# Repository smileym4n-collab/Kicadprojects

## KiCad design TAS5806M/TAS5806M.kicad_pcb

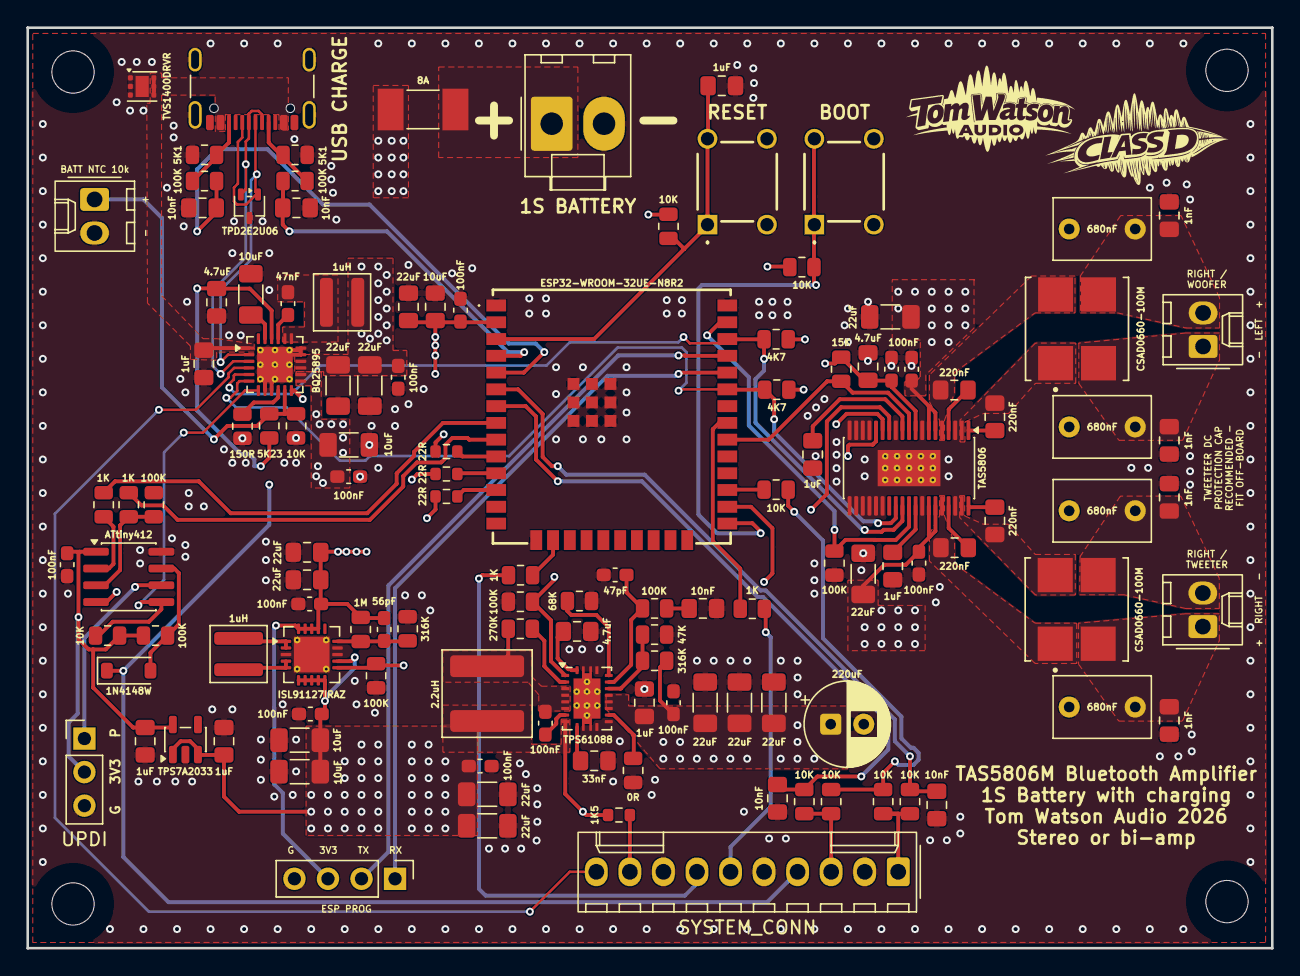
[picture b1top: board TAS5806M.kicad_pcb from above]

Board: 4 copper layers, 94.2 x 69.7 mm, 130 parts (0 on the bottom side), 82 nets.

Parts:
C101, C102, C204, C404, C405: 10nF; C_0805_2012Metric_Pad1.18x1.45mm_HandSolder
C103, C109, C302, C303: 10uF; C_1206_3216Metric_Pad1.33x1.80mm_HandSolder
C104: 47nF; C_0603_1608Metric_Pad1.08x0.95mm_HandSolder
C105, C209, C401, C402, C501, C614, C615: 1uF; C_0805_2012Metric_Pad1.18x1.45mm_HandSolder
C106, C107, C206, C207, C210, C211, C212, C616, C618: 22uF; C_1206_3216Metric_Pad1.33x1.80mm_HandSolder
C108, C111, C201, C208, C213, C304, C307, C403, C504, C617, C619, C622: 100nF; C_0603_1608Metric_Pad1.08x0.95mm_HandSolder
C110, C202, C621: 4.7uF; C_0805_2012Metric_Pad1.18x1.45mm_HandSolder
C203: 33nF; C_0805_2012Metric_Pad1.18x1.45mm_HandSolder
C205: 47pF; C_0603_1608Metric_Pad1.08x0.95mm_HandSolder
C301: 56pF; C_0603_1608Metric_Pad1.08x0.95mm_HandSolder
C305, C306, C502: 22uF; C_0805_2012Metric_Pad1.18x1.45mm_HandSolder
C503: 10uF; C_0805_2012Metric_Pad1.18x1.45mm_HandSolder
C601, C602, C607, C608: 220nF; C_0805_2012Metric_Pad1.18x1.45mm_HandSolder
C603, C604, C609, C610: 680nF; C_Rect_L7.2mm_W4.5mm_P5.00mm_FKS2_FKP2_MKS2_MKP2
C605, C606, C611, C612: 1nF; C_0805_2012Metric_Pad1.18x1.45mm_HandSolder
C620: 220uF; CP_Radial_D6.3mm_P2.50mm
D101: TVS1400DRVR; WSON-6-1EP_2x2mm_P0.65mm_EP1x1.6mm
D401: 1N4148W; D_SOD-123
F101: 8A; Fuse_Littelfuse-NANO2-451_453
H1, H2, H3, H4: MountingHole; MountingHole_3.2mm_M3
J1: ESP PROG; PinHeader_1x04_P2.54mm_Vertical
J2: UPDI; PinHeader_1x03_P2.54mm_Vertical
J101: USB CHARGE; USB_C_Receptacle_GCT_USB4105-xx-A_16P_TopMnt_Horizontal
J102: 1S BATTERY; Molex_KK-396_A-41791-0002_1x02_P3.96mm_Vertical
J103: BATT NTC 10k; Molex_KK-254_AE-6410-02A_1x02_P2.54mm_Vertical
J402: SYSTEM_CONN; Molex_KK-254_AE-6410-10A_1x10_P2.54mm_Vertical
J601: - LEFT +; Molex_KK-254_AE-6410-02A_1x02_P2.54mm_Vertical
J602: + RIGHT -; Molex_KK-254_AE-6410-02A_1x02_P2.54mm_Vertical
L101, L301: 1uH; L_Wuerth_MAPI-4020
L201: 2.2uH; L_Bourns_SRP6060FA_BournsLayout
L601, L602: CSAD0660-100M
R101: 150R; R_0805_2012Metric
R102, R104: 5K1; R_0805_2012Metric
R103, R105, R204, R207, R302, R402, R405, R602: 100K; R_0805_2012Metric
R106: 1K5; R_0603_1608Metric
R107: 5K23; R_0805_2012Metric
R108, R401, R406, R407, R408, R409, R501, R506, R510: 10K; R_0805_2012Metric
R201, R304: 316K; R_0805_2012Metric
R202: 47K; R_0805_2012Metric
R203: 270K; R_0805_2012Metric
R205: 0R; R_0805_2012Metric
R206: 68K; R_0805_2012Metric
R303: 1M; R_0805_2012Metric
R403, R404, R505, R509: 1K; R_0805_2012Metric
R502, R503, R504: 22R; R_0603_1608Metric
R507, R508: 4K7; R_0805_2012Metric
R601: 15K; R_0805_2012Metric
SW501: RESET; TS026650BK100SCRD
SW502: BOOT; TS026650BK100SCRD
U101: BQ25895; Texas_RTW_WQFN-24-1EP_4x4mm_P0.5mm_EP2.7x2.7mm_ThermalVias
U102: TPD2E2U06; SOT-323_SC-70
U201: TPS61088; Texas_VQFN-RHL-20_ThermalVias
U301: ISL91127IRAZ; QFN-20-1EP_4x4mm_P0.5mm_EP2.7x2.7mm_ThermalVias
U401: TPS7A2033; SOT-23-5
U402: ATtiny412; SOIC-8_3.9x4.9mm_P1.27mm
U501: ESP32-WROOM-32UE-N8R2; ESP32WROOM32UEN8R2
U601: TAS5806; HTSSOP-38-1EP_4.4x9.7mm_P0.5mm_EP2.74x4.75mm_ThermalVias

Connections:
+3V3: C301.1, C305.1, C306.1, C307.1, C502.1, C503.1, C504.1, C621.1, C622.1, J1.3, R303.1, R406.2, R408.2, R501.2, R506.2, R507.2, R508.2, R510.2, R601.2, U301.17 (VOUT), U301.18 (VOUT), U301.19 (VOUT), U301.20 (VOUT), U501.2 (3V3), U601.9 (DVDD)
+3V3_AON: C402.1, C403.1, J2.2, R401.2, R402.2, U401.5 (OUT), U402.1 (VCC)
/AMPLIFIER/SPK_L+: C604.1, C606.1, J601.2, L601.3
/AMPLIFIER/SPK_L-: C603.1, C605.1, J601.1, L601.2
/AMPLIFIER/SPK_R+: C609.1, C611.1, J602.1, L602.2
/AMPLIFIER/SPK_R-: C610.1, C612.1, J602.2, L602.3
/ESP32/ESP_EN: C501.1, R501.1, SW501.1 (NO), SW501.2 (NO), U501.3 (EN)
/ESP32/ESP_IO0: R510.1, SW502.1 (NO), SW502.2 (NO), U501.25 (IO0)
/ESP32/ESP_IO16: R506.1, U501.27 (IO16)
/ESP32/ESP_RXD0: J1.1, U501.34 (RXD0)
/ESP32/ESP_TXD0: J1.2, U501.35 (TXD0)
/POWER_CTRL/BTN_N: D401.2 (A), R402.1, U402.7 (PA3)
/USB_CHARGER/CC1: J101.A5 (CC1), R102.1, R103.1
/USB_CHARGER/CC2: J101.B5 (CC2), R104.1, R105.1
/USB_CHARGER/USB_DN: J101.A7 (D-), J101.B7 (D-), U101.3 (D-), U102.2 (IO2)
/USB_CHARGER/USB_DP: J101.A6 (D+), J101.B6 (D+), U101.2 (D+), U102.1 (IO1)
AMP_FAULT_N: R601.1, U501.30 (IO18), U601.10 (ADR/FAULT)
AMP_PDN: R602.1, U501.37 (IO23), U601.29 (PDN)
BOOST_EN: R204.1, U201.2 (EN), U501.26 (IO4)
BTN_RAW_N: D401.1 (K), J402.4, U101.12 (~QON)
BT_LED: J402.7, R505.2
CC1_SENSE: C101.1, R103.2, U501.4 (SENSOR_VP)
CC2_SENSE: C102.1, R105.2, U501.5 (SENSOR_VN)
CHG_INT_N: R401.1, U101.7 (~INT), U402.5 (PA2)
CHG_LED_A: J402.9, R106.1
CHG_LED_K: J402.10, U101.4 (STAT)
ENC_A: C404.1, R407.2, U501.6 (IO34)
ENC_B: C405.1, R409.2, U501.7 (IO35)
EN_3V3: R302.1, U301.11 (EN), U402.4 (PA1)
GND: C101.2, C102.2, C103.2, C105.2, C106.2, C107.2, C108.2, C109.2, C110.2, C111.2, C202.2, C203.2, C204.2, C205.2, C206.2, C207.2, C208.2, C209.2, C210.2, C211.2, C212.2, C213.2, C302.2, C303.2, C304.2, C305.2, C306.2, C307.2, C401.2, C402.2, C403.2, C404.2, C405.2, C501.2, C502.2, C503.2, C504.2, C603.2, C604.2, C605.2, C606.2, C609.2, C610.2, C611.2, C612.2, C614.2, C615.2, C616.2, C617.2, C618.2, C619.2, C620.2, C621.2, C622.2, D101.1 (GND), D101.2 (GND), D101.3 (GND), D101.7 (GND), J1.4, J2.3, J101.A1 (GND), J101.A12 (GND), J101.B1 (GND), J101.B12 (GND), J101.SH (SHIELD), J102.2, J103.2, J402.2, J402.5, J402.8, R101.2, R102.2, R104.2, R108.2, R202.2, R204.2, R205.2, R206.2, R302.2, R304.2, R405.2, R602.2, SW501.3 (COM), SW501.4 (COM), SW502.3 (COM), SW502.4 (COM), U101.8 (OTG), U101.9 (~CE), U101.17 (PGND), U101.18 (PGND), U101.25 (PGND), U102.3 (GND), U201.11 (NC), U201.12 (NC), U201.20 (AGND), U201.21 (PGND), U301.3 (PGND), U301.13 (SGND), U301.14 (SGND), U301.21 (EPAD), U401.2 (GND), U402.8 (GND), U501.1 (GND_1), U501.15 (GND_2), U501.38 (GND_3), U501.39 (GND_4), U501.40 (GND_5), U501.41 (GND_6), U501.42 (GND_7), U501.43 (GND_8), U501.44 (GND_9), U501.45 (GND_10), U501.46 (GND_11), U501.47 (GND_12), U601.3 (PGND), U601.8 (DGND), U601.12 (DGND), U601.16 (NC), U601.17 (NC), U601.18 (NC), U601.19 (NC), U601.20 (NC), U601.21 (NC), U601.22 (NC), U601.23 (NC), U601.24 (NC), U601.25 (NC), U601.31 (AGND), U601.36 (PGND), U601.39 (PAD)
I2C_SCL: R508.1, U101.5 (SCL), U501.36 (IO22), U601.28 (SCL)
I2C_SDA: R507.1, U101.6 (SDA), U501.33 (IO21), U601.27 (SDA)
I2S_BCLK: R503.2, U601.14 (SCLK)
I2S_DOUT: R504.2, U601.15 (SDIN)
I2S_LRCLK: R502.2, U601.13 (LRCLK)
unnamed: C104.1, L101.1, U101.19 (SW), U101.20 (SW)
unnamed: C201.2, L201.2, R203.2, U201.4 (SW), U201.5 (SW), U201.6 (SW), U201.7 (SW)
unnamed: C204.1, R207.2
unnamed: J2.1, U402.6 (~RESET/PA0)
unnamed: F101.1, J102.1
unnamed: J103.1, R107.2, R108.1, U101.11 (TS)
unnamed: J402.1, R406.1, R407.1
unnamed: J402.3, R408.1, R409.1
unnamed: L301.1, U301.4 (LX1), U301.5 (LX1)
unnamed: L301.2, U301.1 (LX2), U301.2 (LX2)
unnamed: C104.2, U101.21 (BTST)
unnamed: R101.1, U101.10 (ILIM)
unnamed: C103.1, U101.23 (PMID)
unnamed: C110.1, R107.1, U101.22 (REGN)
unnamed: C201.1, U201.8 (BOOT)
unnamed: C205.1, R207.1, U201.18 (COMP)
unnamed: R201.2, R202.1, U201.17 (FB)
unnamed: R203.1, U201.3 (FSW)
unnamed: R206.1, U201.19 (ILIM)
unnamed: R205.1, U201.13 (MODE)
unnamed: C203.1, U201.10 (SS)
unnamed: C202.1, U201.1 (VCC)
unnamed: C301.2, R303.2, R304.1, U301.15 (FB)
unnamed: R403.1, U402.2 (PA6)
unnamed: R404.1, R405.1, U402.3 (PA7)
unnamed: R505.1, U501.16 (IO13)
unnamed: R509.1, U501.31 (IO19)
unnamed: R502.1, U501.10 (IO25)
unnamed: R503.1, U501.11 (IO26)
unnamed: R504.1, U501.12 (IO27)
unnamed: C615.1, U601.30 (AVDD)
unnamed: C601.1, U601.4 (BST_A+)
unnamed: C602.1, U601.1 (BST_A-)
unnamed: C607.1, U601.35 (BST_B+)
unnamed: C608.1, U601.38 (BST_B-)
unnamed: C601.2, L601.4, U601.5 (OUT_A+)
unnamed: C602.2, L601.1, U601.2 (OUT_A-)
unnamed: C607.2, L602.1, U601.34 (OUT_B+)
unnamed: C608.2, L602.4, U601.37 (OUT_B-)
unnamed: C614.1, U601.11 (VR_DIG)
PC_RX: R404.2, U501.9 (IO33)
PC_TX: R403.2, U501.8 (IO32)
PVDD: C209.1, C210.1, C211.1, C212.1, C213.1, C616.1, C617.1, C618.1, C619.1, C620.1, R201.1, U201.14 (VOUT), U201.15 (VOUT), U201.16 (VOUT), U601.6 (PVDD), U601.7 (PVDD), U601.32 (PVDD), U601.33 (PVDD)
PWR_LED: J402.6, R509.2
VBAT: C109.1, C111.1, F101.2, U101.13 (BAT), U101.14 (BAT)
VBUS: C105.1, D101.4 (IN), D101.5 (IN), D101.6 (IN), J101.A4 (VBUS), J101.A9 (VBUS), J101.B4 (VBUS), J101.B9 (VBUS), U101.1 (VBUS)
VSYS: C106.1, C107.1, C108.1, C206.1, C207.1, C208.1, C302.1, C303.1, C304.1, C401.1, L101.2, L201.1, R106.2, U101.15 (SYS), U101.16 (SYS), U201.9 (VIN), U301.6 (PVIN), U301.7 (PVIN), U301.8 (PVIN), U301.9 (PVIN), U301.10 (VIN), U301.12 (MODE), U401.1 (IN), U401.3 (EN)

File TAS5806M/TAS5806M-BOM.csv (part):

"Refs","Value","Footprint","Manufacturer","MPN","Stock","Note","Qty","DNP"
"C101,C102,C204,C404,C405","10n","Capacitor_SMD:C_0805_2012Metric_Pad1.18x1.45mm_HandSolder","Walsin","0805N103J500CT","Inventory id 88 (qty 38)","50 V NP0","5",""
"C103","10u","Capacitor_SMD:C_1206_3216Metric_Pad1.33x1.80mm_HandSolder","Samsung","CL31A106KBHNNNE","Inventory id 505 (qty 10)","50 V X5R","1",""
"C104","47n","Capacitor_SMD:C_0603_1608Metric_Pad1.08x0.95mm_HandSolder","Murata","GRM188R71H473KA61D","Purchase","50 V X7R (BTST)","1",""
"C105,C209,C401,C402,C501,C614,C615","1u","Capacitor_SMD:C_0805_2012Metric_Pad1.18x1.45mm_HandSolder","Samsung","CL21B105KAFNNNG","Purchase (user standard 2012; inventory 3216 CL31B105KBHNFNE x50 fallback)","25 V X7R","7",""
"C106,C107,C206,C207,C210-C212,C616,C618","22u","Capacitor_SMD:C_1206_3216Metric_Pad1.33x1.80mm_HandSolder","Samsung","CL31A226KAHNNNE","Inventory id 202 (qty 19)","25 V X5R","9",""
"C108,C111,C201,C208,C213,C304,C307,C403,C504,C617,C619,C622","100n","Capacitor_SMD:C_0603_1608Metric_Pad1.08x0.95mm_HandSolder","KEMET","C0603C104M5RACTU","Purchase (user standard 1608; inventory has 3216 C1206C104K5RACTU x129 as fallback)","50 V X7R","12",""
"C109,C302,C303","10u","Capacitor_SMD:C_1206_3216Metric_Pad1.33x1.80mm_HandSolder","Taiyo Yuden","TMK316B7106KL-TD","Inventory id 135 (qty 50)","25 V X7R","3",""
"C110,C202,C621","4u7","Capacitor_SMD:C_0805_2012Metric_Pad1.18x1.45mm_HandSolder","Samsung","CL21A475KAQNNNE","Inventory id 133 (qty 50)","25 V X5R","3",""
"C203","33n","Capacitor_SMD:C_0805_2012Metric_Pad1.18x1.45mm_HandSolder","Murata","GRM2165C1H333JA01D","Inventory id 567 (qty 20)","50 V C0G","1",""
"C205","47p DNP","Capacitor_SMD:C_0603_1608Metric_Pad1.08x0.95mm_HandSolder","Murata","GRM1885C1H470JA01D","DNP - DNP (tuning footprint)","50 V C0G","1","DNP"
"C301","56p","Capacitor_SMD:C_0603_1608Metric_Pad1.08x0.95mm_HandSolder","Murata","GRM1885C1H560JA01D","Purchase","50 V C0G","1",""
"C305,C306,C502","22u","Capacitor_SMD:C_0805_2012Metric_Pad1.18x1.45mm_HandSolder","Murata","(inventory id 339, MPN not recorded)","Inventory id 339 (qty 39)","10 V X5R","3",""
"C503","10u","Capacitor_SMD:C_0805_2012Metric_Pad1.18x1.45mm_HandSolder","Samsung","CL21A106KOQNNNF","Inventory id 184 (qty 32)","16 V X5R","1",""
"C601,C602,C607,C608","220n","Capacitor_SMD:C_0805_2012Metric_Pad1.18x1.45mm_HandSolder","Samsung","CL21B224KAFNNNE","Inventory id 84 (qty 48)","25 V X7R","4",""
"C603,C604,C609,C610","680n FILM","Capacitor_THT:C_Rect_L7.2mm_W4.5mm_P5.00mm","KEMET","R82DC3680Z360J","Purchase - CPC (in stock per user)","63 VDC metallised PET film, 5%, 5 mm pitch, 7.2x4.5x9.5 mm; mount flush, short GND via","4",""
"C605,C606,C611,C612","1n","Capacitor_SMD:C_0805_2012Metric_Pad1.18x1.45mm_HandSolder","Multicomp Pro","MC0805N102J500CT","Inventory id 558 (qty 100)","50 V C0G","4",""
"C620","220u","Capacitor_THT:CP_Radial_D6.3mm_P2.50mm","Panasonic","EEUFR1C221B","Inventory id 581 (qty 10)","16 V FR series low-ESR; confirm 6.3 mm body","1",""
"D101","TVS1400DRVR","Package_SON:WSON-6-1EP_2x2mm_P0.65mm_EP1x1.6mm","Texas Instruments","TVS1400DRVR","Purchase","","1",""
"D102","RED","LED_SMD:LED_0805_2012Metric","Kingbright","KP-2012EC","Inventory id 640 (qty 10)","","1",""
"D401","1N4148W","Diode_SMD:D_SOD-123","onsemi","1N4148W","Inventory id 510 (qty 67)","","1",""
"D501","GREEN","LED_SMD:LED_0805_2012Metric","Kingbright","KP-2012LSGC","Inventory id 639 (qty 1)","2 mA low-current type","1",""
"F101","8A","Fuse:Fuse_Littelfuse-NANO2-451_453","Littelfuse","0451008.MRL","Purchase","8 A very fast, 7.7 mOhm, 125 V","1",""
"J101","USB4105-GF-A","Connector_USB:USB_C_Receptacle_GCT_USB4105-xx-A_16P_TopMnt_Horizontal","GCT","USB4105-GF-A","Purchase","5 A rated USB 2.0 Type-C receptacle","1",""
"J102","BATTERY 1S","Connector_Molex:Molex_KK-396_A-41791-0002_1x02_P3.96mm_Vertical","Molex","09-65-2028 (41791-0002)","Inventory id 722 (qty 16)","KK-396 friction-lock, polarised; pin 1 = BAT+","1",""
"J103","BATT NTC 10k","Connector_Molex:Molex_KK-254_AE-6410-02A_1x02_P2.54mm_Vertical","Multicomp Pro","MC34629 (+ housing MC34481)","Inventory id 126 (qty 40)","2.54 mm friction-lock header; verify footprint vs MC34629 drawing","1",""
"J401","UPDI","Connector_Molex:Molex_KK-254_AE-6410-03A_1x03_P2.54mm_Vertical","Multicomp Pro","MC34631 (+ housing MC34483)","Inventory id 127 (qty 40)","","1",""
"J501","ESP PROG","Connector_PinHeader_2.54mm:PinHeader_1x06_P2.54mm_Vertical","Multicomp Pro","MC34635","Inventory id 691 (qty 10)","","1",""
"J601","SPEAKER L","Connector_Molex:Molex_KK-254_AE-6410-02A_1x02_P2.54mm_Vertical","Multicomp Pro","MC34629 (+ housing MC34481)","Inventory id 126 (qty 40)","2.54 mm friction-lock header; verify footprint vs MC34629 drawing","1",""
"J602","SPEAKER R","Connector_Molex:Molex_KK-254_AE-6410-02A_1x02_P2.54mm_Vertical","Multicomp Pro","MC34629 (+ housing MC34481)","Inventory id 126 (qty 40)","2.54 mm friction-lock header; verify footprint vs MC34629 drawing","1",""
"L101,L301","1u","Inductor_SMD:L_Coilcraft_XAL4020-XXX","Coilcraft","XFL4020-102MEB","Purchase","1.0 uH, DCR 11.9 mOhm max, Isat 4.5/5.4 A (10/30%); footprint = XAL4020 land pattern, verify vs Coilcraft doc 745","2",""
"L201","2u2","Inductor_SMD:L_Coilcraft_XAL7030-222","Coilcraft","XAL7030-222MEB","Purchase","2.2 uH, DCR 15.07 mOhm max, Isat 18 A, Irms 10 A","1",""
"L601,L602","CSAD0660-100M","Soundbar:CSAD0660-100M","Codaca","CSAD0660-100M","Inventory id 520 (qty 2)","2 x 10 uH, DCR 47 mOhm typ, Isat 6.5 A, Irms 3.5 A","2",""
"R101","150R","Resistor_SMD:R_0805_2012Metric","Yageo","RC0805FR-07150RL","Purchase (stock 150R id 211 has no recorded tolerance)","1%; sets BQ25895 ILIM ceiling","1",""
"R102,R104","5k1","Resistor_SMD:R_0805_2012Metric","Yageo","RC0805FR-135K1L","Inventory id 374 (qty 100)","1% thick film","2",""
"R103,R105,R204,R302,R402,R405,R602","100k","Resistor_SMD:R_0805_2012Metric","(unknown)","100K thick film 2012","Inventory id 241 (qty 77)","5% thick film","7",""
"R106","1k5","Resistor_SMD:R_0603_1608Metric","(unknown)","1K5 thick film 1608","Inventory id 226 (qty 65)","1% thick film","1",""
"R107","5k23","Resistor_SMD:R_0805_2012Metric","Stackpole","RMCF0805FT5K23","Inventory id 568 (qty 100)","1% thick film","1",""
"R108","30k","Resistor_SMD:R_0805_2012Metric","Stackpole","RMCF0805FT30K0","Inventory id 573 (qty 100)","1% thick film","1",""
"R201,R304","316k","Resistor_SMD:R_0805_2012Metric","(unknown)","316K thick film 2012","Inventory id 245 (qty 49)","1% thick film","2",""
"R202","47k","Resistor_SMD:R_0805_2012Metric","Stackpole","RMCF0805FT47K0","Inventory id 504 (qty 100)","1% thick film","1",""
"R203","270k","Resistor_SMD:R_0805_2012Metric","(unknown)","270K thick film 2012","Inventory id 249 (qty 94)","5% (sets fsw only)","1",""
"R205","0R DNP","Resistor_SMD:R_0805_2012Metric","(unknown)","0R link 2012","DNP - Inventory id 204 (DNP option)","DNP","1","DNP"
"R206","68k","Resistor_SMD:R_0805_2012Metric","Yageo","RC0805FR-0768KL","Purchase","1%; TPS61088 peak current limit","1",""
"R207","100k","Resistor_SMD:R_0805_2012Metric","(unknown)","100K thin film 2012","Inventory id 242 (qty 70)","0.5% thin film","1",""
"R303","1M","Resistor_SMD:R_0805_2012Metric","(unknown)","1M thin film 2012","Inventory id 247 (qty 40)","0.5% thin film","1",""
"R401,R406-R409,R501,R506","10k","Resistor_SMD:R_0805_2012Metric","KOA Speer","RK73B2ATTD103J","Inventory id 194 (qty 100)","5% thick film","7",""
"R403,R404,R505","1k","Resistor_SMD:R_0805_2012Metric","(unknown)","1K thick film 2012","Inventory id 223 (qty 75)","5% thick film","3",""
"R502-R504","22R","Resistor_SMD:R_0603_1608Metric","KOA Speer","RK73B1JTTD220J","Inventory id 185 (qty 150)","5% thick film","3",""
"R507,R508","4k7","Resistor_SMD:R_0805_2012Metric","Stackpole","RMCF0805FT4K70","Inventory id 493 (qty 100)","1% thick film","2",""
"R601","15k","Resistor_SMD:R_0805_2012Metric","(unknown)","15K thin film 2012","Inventory id 235 (qty 22)","0.5% thin film","1",""
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
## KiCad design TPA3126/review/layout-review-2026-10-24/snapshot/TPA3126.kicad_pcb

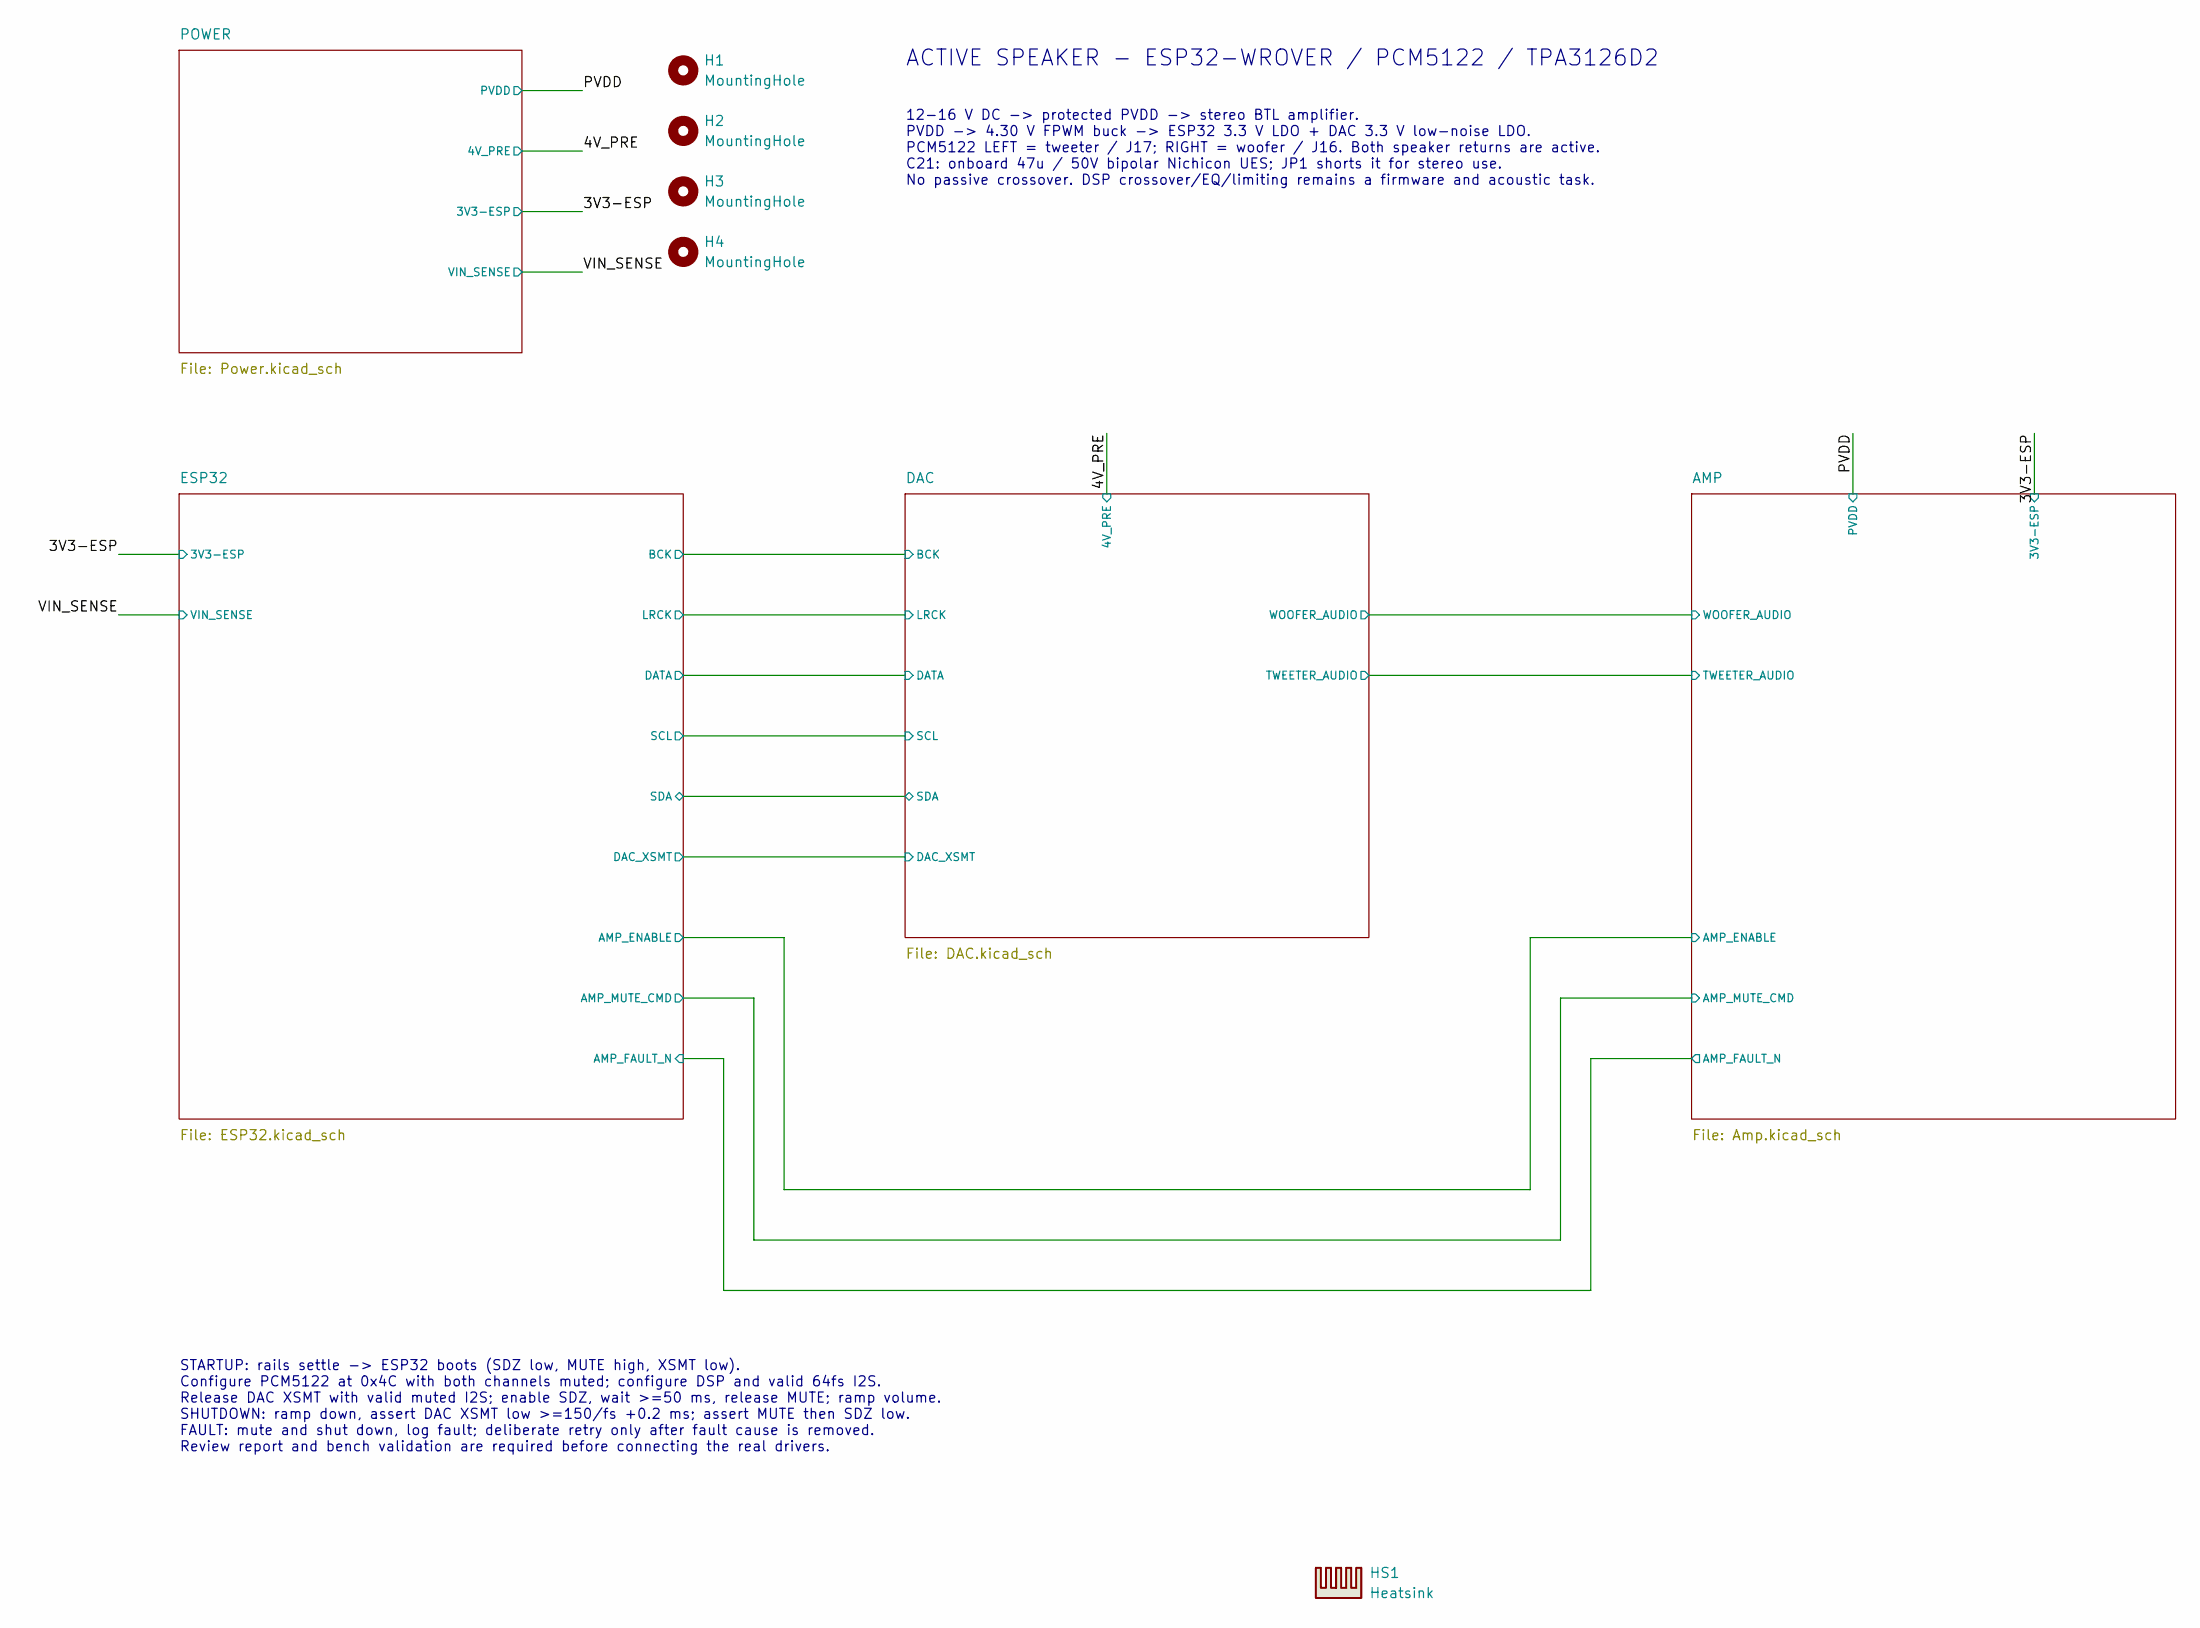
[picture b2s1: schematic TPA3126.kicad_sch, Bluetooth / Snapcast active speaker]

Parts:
H1, H2, H3, H4: MountingHole; MountingHole_3.2mm_M3
HS1: Heatsink; Heatsink_ATS_ATS-TI1OP-521-C1-R1_50x13.9mm_H25mm_P40mm; MPN ATS-TI1OP-521-C1-R1

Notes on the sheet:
STARTUP: rails settle -> ESP32 boots (SDZ low, MUTE high, XSMT low). Configure PCM5122 at 0x4C with both channels muted; configure DSP and valid 64fs I2S. Release DAC XSMT with valid muted I2S; enable SDZ, wait >=50 ms, release MUTE; ramp volume. SHUTDOWN: ramp down, assert DAC XSMT low >=150/fs +0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
ACTIVE SPEAKER - ESP32-WROVER / PCM5122 / TPA3126D2
12-16 V DC -> protected PVDD -> stereo BTL amplifier. PVDD -> 4.30 V FPWM buck -> ESP32 3.3 V LDO + DAC 3.3 V low-noise LDO. PCM5122 LEFT = tweeter / J17; RIGHT = woofer / J16. Both speaker returns are active. C21: onboard 47u / 50V bipolar Nichicon UES; JP1 shorts it for stereo use. No passive cro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

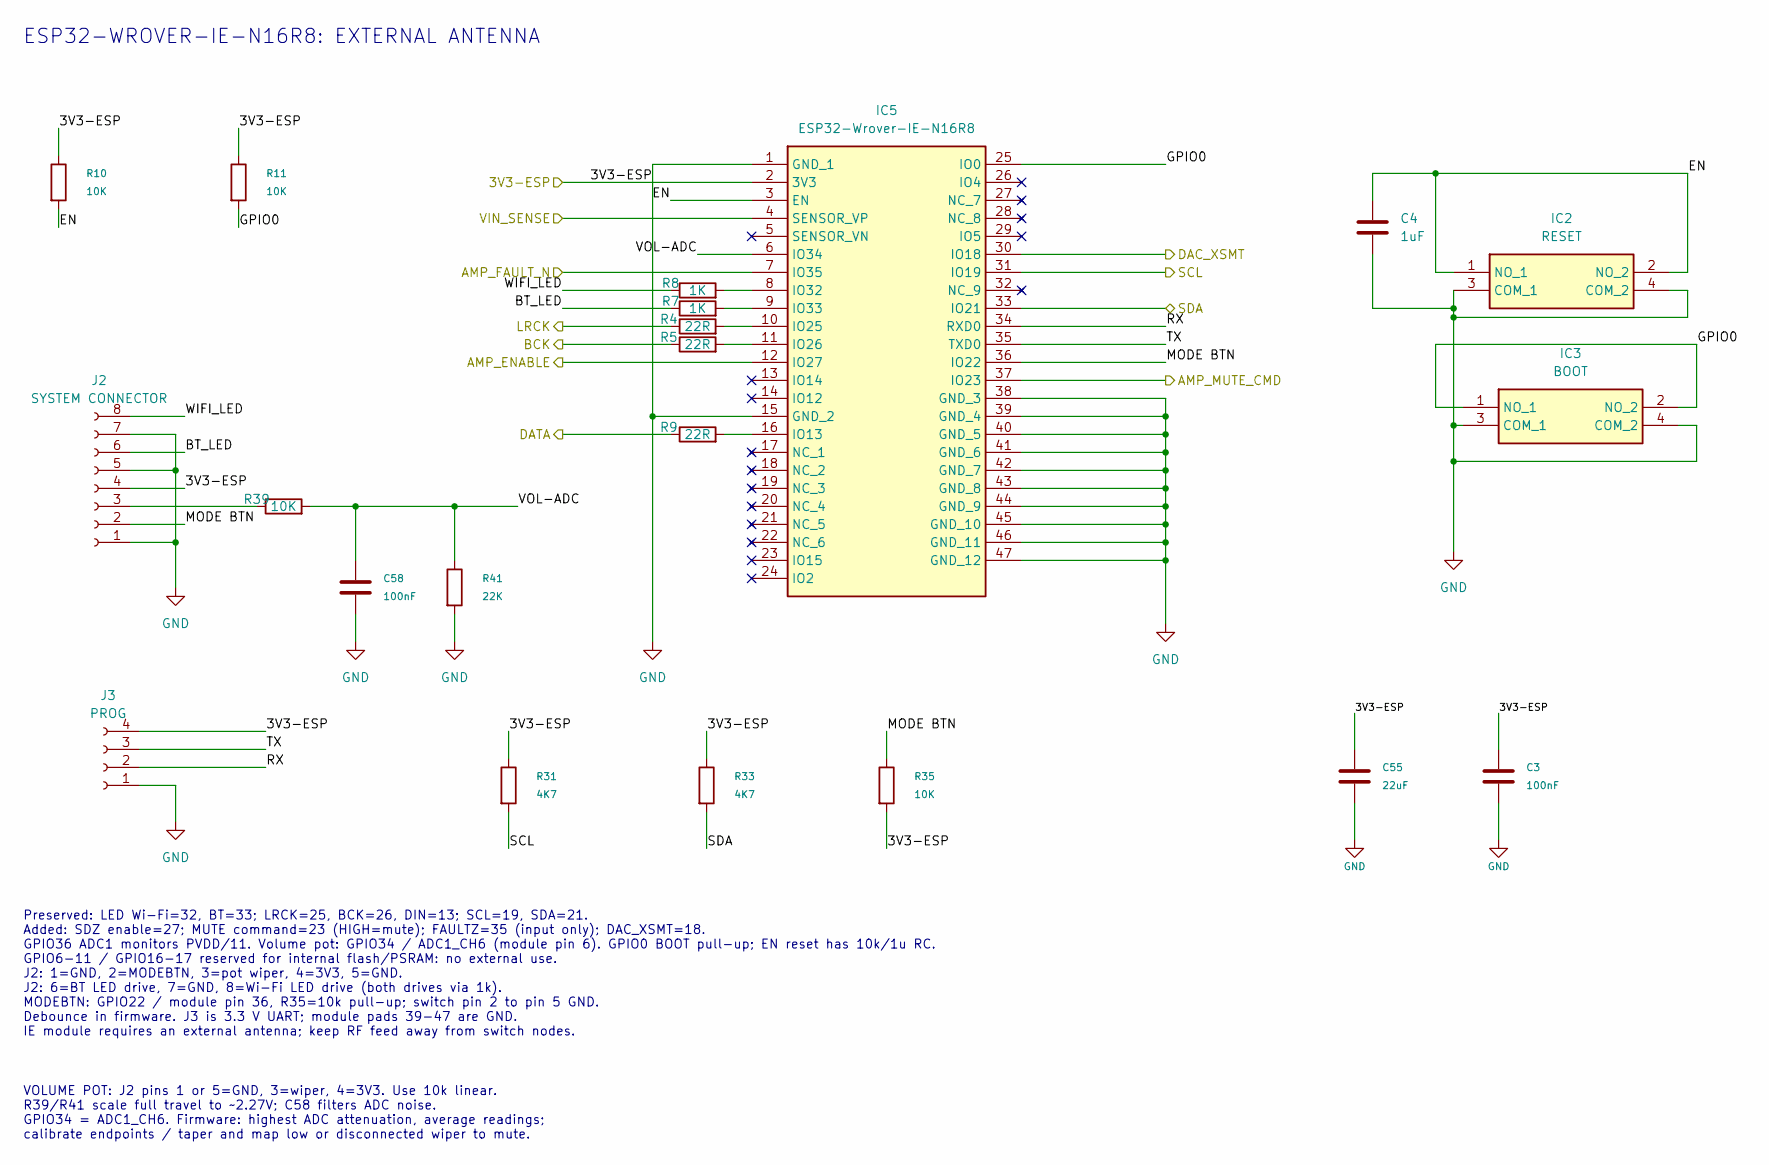
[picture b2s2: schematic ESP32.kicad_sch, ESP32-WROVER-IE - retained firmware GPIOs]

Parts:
C3, C58: 100nF; C_1206_3216Metric_Pad1.33x1.80mm_HandSolder; MPN C1206C104K5RACTU
C4: 1uF; C_1206_3216Metric_Pad1.33x1.80mm_HandSolder; MPN CL31B105KBHNFNE
C55: 22uF; C_1206_3216Metric_Pad1.33x1.80mm_HandSolder; MPN CL31A226KAHNNNE
IC2: RESET; TS026650BK100SCRD; Mouser Part Number 179-TS026650BK100SCR
IC3: BOOT; TS026650BK100SCRD; Mouser Part Number 179-TS026650BK100SCR
IC5: ESP32-Wrover-IE-N16R8; ESP32-WROVER-IE-N16R8; Mouser Part Number 356-ESP32WRVIE2864UC
J2: SYSTEM CONNECTOR; JST_XH_B8B-XH-A_1x08_P2.50mm_Vertical; MPN B8B-XH-A(LF)(SN)
J3: PROG; PinHeader_1x04_P2.54mm_Vertical
R4, R5, R9: 22R; R_0603_1608Metric_Pad0.98x0.95mm_HandSolder; MPN RK73B1JTTD220J
R7, R8: 1K; R_0805_2012Metric_Pad1.20x1.40mm_HandSolder
R10, R11, R35: 10K; R_0603_1608Metric_Pad0.98x0.95mm_HandSolder
R31, R33: 4K7; R_0805_2012Metric_Pad1.20x1.40mm_HandSolder; MPN RMCF0805FT4K70
R39: 10K; R_0805_2012Metric_Pad1.20x1.40mm_HandSolder; MPN RK73B2ATTD103J
R41: 22K; R_0805_2012Metric_Pad1.20x1.40mm_HandSolder; MPN RR1220P-223-D

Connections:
/3V3-ESP: C3.1, C55.1, IC5.2 (3V3), J2.4, J3.4, R10.1, R11.1, R31.1, R33.1, R35.2; also elsewhere on the board
/AMP/AMP_ENABLE: IC5.12 (IO27); also elsewhere on the board
/AMP/AMP_FAULT_N: IC5.7 (IO35); also elsewhere on the board
/AMP/AMP_MUTE_CMD: IC5.37 (IO23); also elsewhere on the board
/DAC/BCK: R5.1; also elsewhere on the board
/DAC/DAC_XSMT: IC5.30 (IO18); also elsewhere on the board
/DAC/DATA: R9.1; also elsewhere on the board
/DAC/LRCK: R4.1; also elsewhere on the board
/ESP32/BT_LED: J2.6, R7.1
/ESP32/EN: C4.1, IC2.1 (NO_1), IC2.2 (NO_2), IC5.3 (EN), R10.2
/ESP32/GPIO0: IC3.1 (NO_1), IC3.2 (NO_2), IC5.25 (IO0), R11.2
/ESP32/MODE BTN: IC5.36 (IO22), J2.2, R35.1
/ESP32/RX: IC5.34 (RXD0), J3.2
/ESP32/SCL: IC5.31 (IO19), R31.2; also elsewhere on the board
/ESP32/SDA: IC5.33 (IO21), R33.2; also elsewhere on the board
/ESP32/TX: IC5.35 (TXD0), J3.3
/ESP32/VOL-ADC: C58.1, IC5.6 (IO34), R39.2, R41.1
/ESP32/WIFI_LED: J2.8, R8.1
/VIN_SENSE: IC5.4 (SENSOR_VP); also elsewhere on the board
GND: C3.2, C4.2, C55.2, C58.2, IC2.3 (COM_1), IC2.4 (COM_2), IC3.3 (COM_1), IC3.4 (COM_2), IC5.1 (GND_1), IC5.15 (GND_2), IC5.38 (GND_3), IC5.39 (GND_4), IC5.40 (GND_5), IC5.41 (GND_6), IC5.42 (GND_7), IC5.43 (GND_8), IC5.44 (GND_9), IC5.45 (GND_10), IC5.46 (GND_11), IC5.47 (GND_12), J2.1, J2.5, J2.7, J3.1, R41.2; also elsewhere on the board
unnamed: IC5.16 (IO13), R9.2
unnamed: IC5.10 (IO25), R4.2
unnamed: IC5.11 (IO26), R5.2
unnamed: IC5.8 (IO32), R8.2
unnamed: IC5.9 (IO33), R7.2
unnamed: J2.3, R39.1

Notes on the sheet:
ESP32-WROVER-IE-N16R8: EXTERNAL ANTENNA
VOLUME POT: J2 pins 1 or 5=GND, 3=wiper, 4=3V3. Use 10k linear. R39/R41 scale full travel to ~2.27V; C58 filters ADC noise. GPIO34 = ADC1_CH6. Firmware: highest ADC attenuation, average readings; calibrate endpoints / taper and map low or disconnected wiper to mute.
Preserved: LED Wi-Fi=32, BT=33; LRCK=25, BCK=26, DIN=13; SCL=19, SDA=21. Added: SDZ enable=27; MUTE command=23 (HIGH=mute); FAULTZ=35 (input only); DAC_XSMT=18. GPIO36 ADC1 monitors PVDD/11. Volume pot: GPIO34 / ADC1_CH6 (module pin 6). GPIO0 BOOT pull-up; EN reset has 10k/1u RC. GPIO6-11 / GPIO16-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

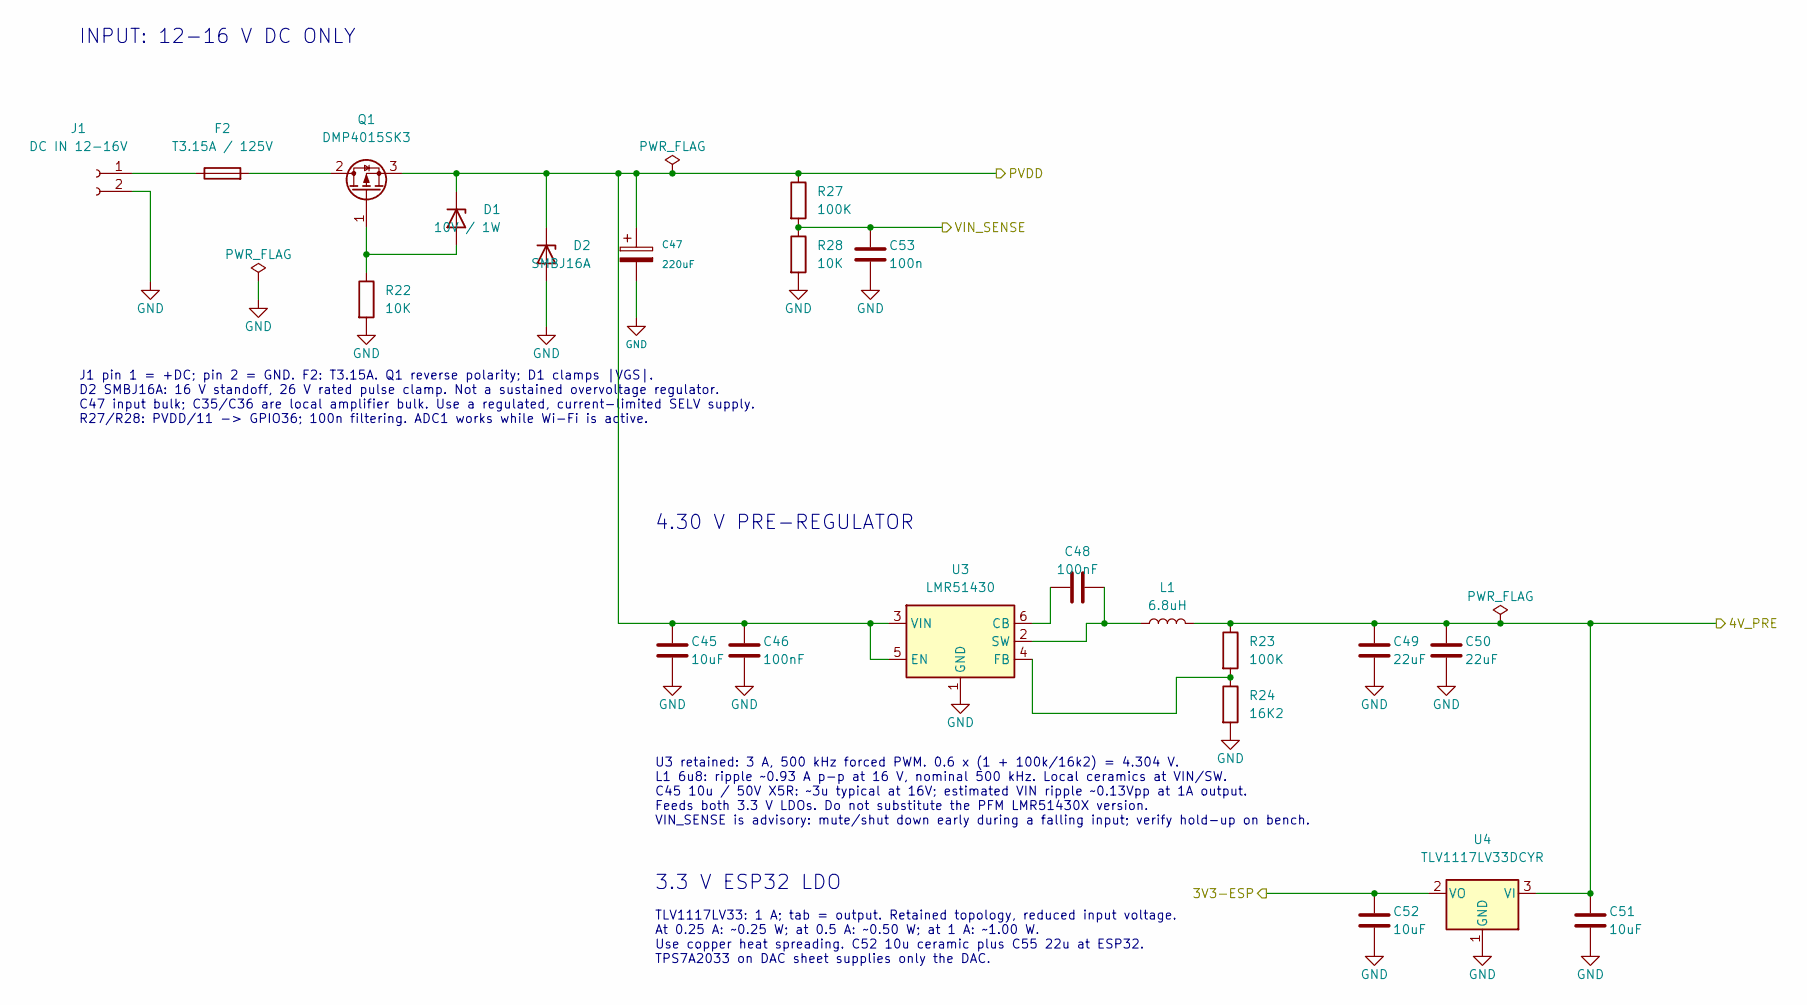
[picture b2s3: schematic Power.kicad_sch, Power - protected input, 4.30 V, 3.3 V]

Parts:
C45: 10uF; C_1206_3216Metric_Pad1.33x1.80mm_HandSolder; Voltage_Rating 50 V; Tolerance 10%; Manufacturer_Part_Number CL31A106KBHNNNE
C46, C48: 100nF; C_0603_1608Metric_Pad1.08x0.95mm_HandSolder; Manufacturer_Part_Number MC0603B104K500CT
C47: 220uF; CP_Radial_D8.0mm_P3.50mm; MPN 35ZLH220MEFC8X11.5
C49, C50: 22uF; C_1206_3216Metric_Pad1.33x1.80mm_HandSolder; Manufacturer_Part_Number CL31A226KAHNNNE
C51, C52: 10uF; C_0805_2012Metric_Pad1.18x1.45mm_HandSolder; Manufacturer_Part_Number CL21A106KOQNNNF
C53: 100n; C_0603_1608Metric_Pad1.08x0.95mm_HandSolder; Manufacturer_Part_Number MC0603B104K500CT
D1: 10V / 1W; D_DO-41_SOD81_P10.16mm_Horizontal; Manufacturer_Part_Number 1N4740ATR
D2: SMBJ16A; D_SMB; Manufacturer_Part_Number SMBJ16A
F2: T3.15A / 125V; Fuse_Littelfuse_395Series; MPN 39613150000
J1: DC IN 12-16V; Molex_KK-396_5273-02A_1x02_P3.96mm_Vertical; Manufacturer_Part_Number 09-65-2028
L1: 6.8uH; SRP6030WA-6R8M; Manufacturer_Part_Number SRP6030WA-6R8M
Q1: DMP4015SK3; TO-252-2; Manufacturer_Part_Number DMP4015SK3-13
R22, R28: 10K; R_0603_1608Metric_Pad0.98x0.95mm_HandSolder; Manufacturer_Part_Number RC0603FR-0710KL
R23, R27: 100K; R_0603_1608Metric_Pad0.98x0.95mm_HandSolder; Manufacturer_Part_Number RC0603FR-07100KL
R24: 16K2; R_0603_1608Metric_Pad0.98x0.95mm_HandSolder; Manufacturer_Part_Number RC0603FR-0716K2L
U3: LMR51430; TSOT-23-6; Manufacturer_Part_Number LMR51430XFDDCR
U4: TLV1117LV33DCYR; SOT-223-3_TabPin2; Manufacturer_Part_Number TLV1117LV33DCYR

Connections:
/3V3-ESP: C52.1, U4.2 (VO); also elsewhere on the board
/4V_PRE: C49.1, C50.1, C51.1, L1.2, R23.1, U4.3 (VI); also elsewhere on the board
/PVDD: C45.1, C46.1, C47.1, D1.1 (K), D2.1 (K), Q1.3 (S), R27.1, U3.3 (VIN), U3.5 (EN); also elsewhere on the board
/VIN_SENSE: C53.1, R27.2, R28.1; also elsewhere on the board
GND: C45.2, C46.2, C47.2, C49.2, C50.2, C51.2, C52.2, C53.2, D2.2 (A), J1.2, R22.2, R24.2, R28.2, U3.1 (GND), U4.1 (GND); also elsewhere on the board
unnamed: D1.2 (A), Q1.1 (G), R22.1
unnamed: F2.1, J1.1
unnamed: F2.2, Q1.2 (D)
unnamed: C48.1, U3.6 (CB)
unnamed: R23.2, R24.1, U3.4 (FB)
unnamed: C48.2, L1.1, U3.2 (SW)

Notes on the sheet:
4.30 V PRE-REGULATOR
3.3 V ESP32 LDO
INPUT: 12-16 V DC ONLY
U3 retained: 3 A, 500 kHz forced PWM. 0.6 x (1 + 100k/16k2) = 4.304 V. L1 6u8: ripple ~0.93 A p-p at 16 V, nominal 500 kHz. Local ceramics at VIN/SW. C45 10u / 50V X5R: ~3u typical at 16V; estimated VIN ripple ~0.13Vpp at 1A output. Feeds both 3.3 V LDOs. Do not substitute the PFM LMR51430X version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
TLV1117LV33: 1 A; tab = output. Retained topology, reduced input voltage. At 0.25 A: ~0.25 W; at 0.5 A: ~0.50 W; at 1 A: ~1.00 W. Use copper heat spreading. C52 10u ceramic plus C55 22u at ESP32. TPS7A2033 on DAC sheet supplies only the DAC.
J1 pin 1 = +DC; pin 2 = GND. F2: T3.15A. Q1 reverse polarity; D1 clamps |VGS|. D2 SMBJ16A: 16 V standoff, 26 V rated pulse clamp. Not a sustained overvoltage regulator. C47 input bulk; C35/C36 are local amplifier bulk. Use a regulated, current-limited SELV supply. R27/R28: PVDD/11 -> GPIO36; 100n f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
